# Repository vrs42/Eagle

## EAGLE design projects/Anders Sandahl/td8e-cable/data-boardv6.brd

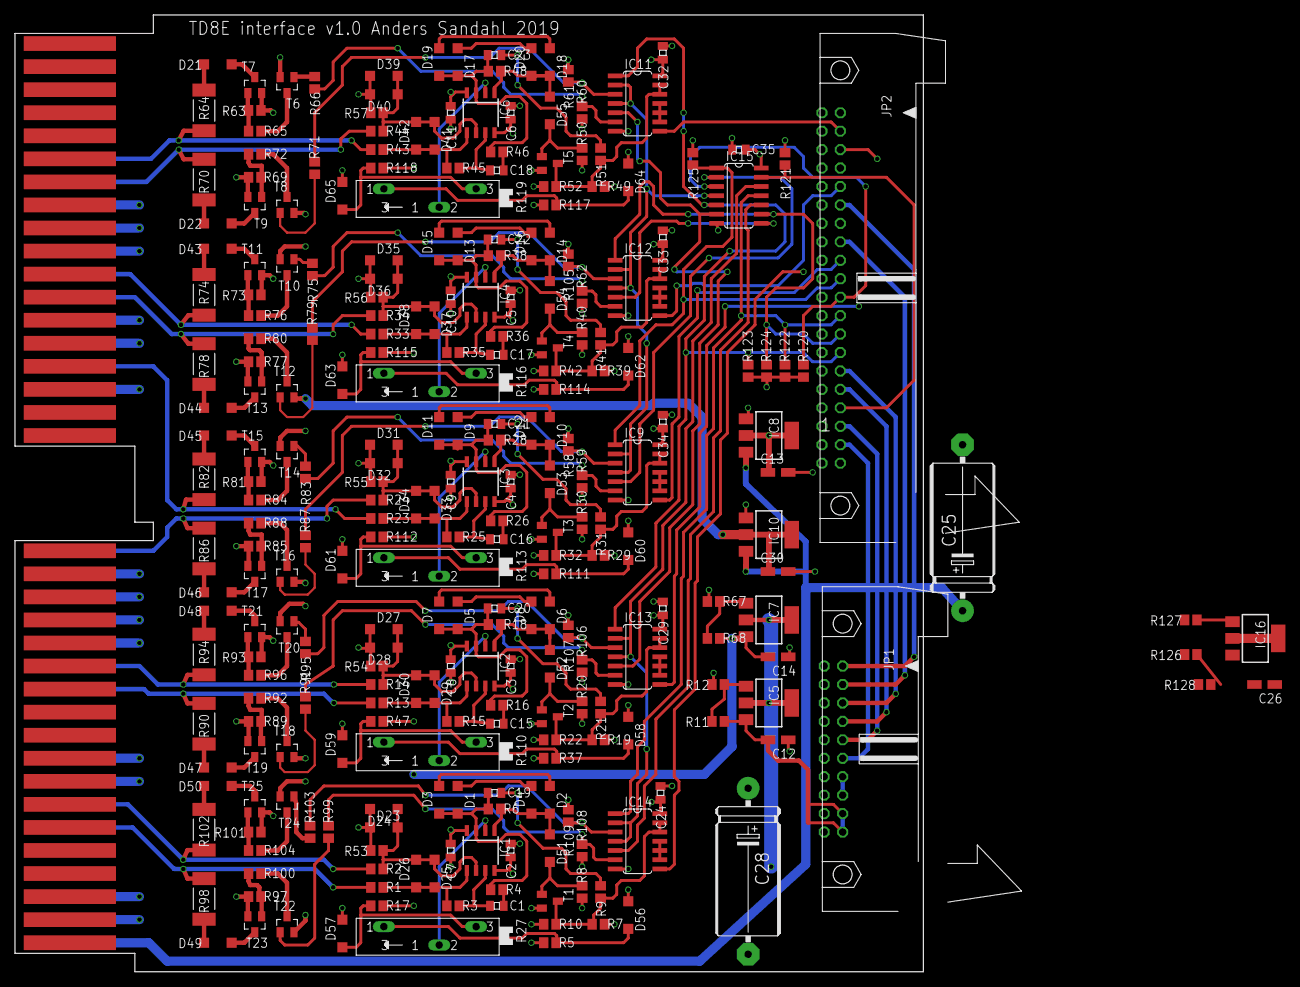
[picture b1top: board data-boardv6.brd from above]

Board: 4 copper layers, 125.1 x 131.8 mm, 270 parts (0 on the bottom side), 179 nets.

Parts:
C1, C15, C16, C17, C18: 10n; 0805
C2, C3, C4, C5, C6, C7, C8, C9, C10, C11, C24, C29, C32, C33, C34, C35: 100n; 0805
C12, C13, C14, C26, C30: 10u/10V; CT3216
C19, C20, C21, C22, C23: 10p; 0805
C25, C28: 330u; E22-9
D1, D2, D3, D4, D5, D6, D7, D8, D9, D10, D11, D12, D13, D14, D15, D16, D17, D18, D19, D20, D23, D24, D25, D26, D27, D28, D29, D30, D31, D32, D33, D34, D35, D36, D37, D38, D39, D40, D41, D42, D51, D52, D53, D54, D55, D56, D57, D58, D59, D60, D61, D62, D63, D64, D65: 1N4148; SOD123
D21, D22, D43, D44, D45, D46, D47, D48, D49, D50: MBR0540T1; SOD123
IC1, IC2, IC3, IC4, IC6: OPA2134D; SOIC8
IC5: LM337; SOT223@1
IC7: LM337; SOT223@2
IC8: LM1117-5; SOT223@3
IC9, IC11, IC12, IC13, IC14: 7400D; SO14
IC10: LM1117-3.3; SOT223@3
IC15: 7404D; SO14
IC16: LM337; SOT223
J1: FLIPCHIP_2; FLIPCHIP-21
JP1: 2Z10/90-FRAMED
JP2: 2X20/90-FRAMED
R1, R2, R13, R14, R23, R24, R33, R34, R43, R44: 220; R0805
R3, R15, R25, R35, R45, R53, R54, R55, R56, R57: 22k; R0805
R4, R8, R16, R20, R26, R30, R36, R40, R46, R50: 4k7; R0805
R5, R17, R37, R47, R111, R112, R114, R115, R117, R118: 2k2; R0805
R6, R9, R18, R21, R28, R31, R38, R41, R48, R51: 470k; R0805
R7, R19, R29, R39, R49: 3k; R0805
R10, R22, R32, R42, R52, R58, R59, R60, R61, R62, R105, R106, R107, R108, R109: 1k; R0805
R11, R68, R127: 240; R0805
R12: 330; R0805
R27, R110, R113, R116, R119: 10k; SP19L
R63, R69, R73, R77, R81, R85, R89, R93, R97, R101: 150; R0805
R64, R70, R74, R78, R82, R86, R90, R94, R98, R102: 75 2W; R2512
R65, R72, R76, R80, R84, R88, R92, R96, R100, R104: 680; R0805
R66, R71, R75, R79, R83, R87, R91, R95, R99, R103: 6k8; R0805
R67: 720; R0805
R120, R121, R122, R123, R124, R125: 470; R0805
R126: 2k05; R0805
R128: 1k8; R0805
T1, T2, T3, T4, T5: BC847; SOT23
T6, T8, T10, T12, T14, T16, T18, T20, T22, T24: BC857B; SOT23
T7, T9, T11, T13, T15, T17, T19, T21, T23, T25: IRLML0100TR; SOT23

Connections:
+3.3V: C30.+, IC10.2, IC10.4, T6.2, T8.2, T10.2, T12.2, T14.2, T16.2, T18.2, T20.2, T22.2, T24.2
+10V: C25.+, IC8.3, IC10.3, J1.AA2
-3V: C12.-, IC5.3, JP1.18, JP1.20, R11.1
-12V: C26.-, IC16.3, R63.1, R69.1, R73.1, R77.1, R81.1, R85.1, R89.1, R93.1, R97.1, R101.1, R127.2, R128.2, T7.2, T9.2, T11.2, T13.2, T15.2, T17.2, T19.2, T21.2, T23.2, T25.2
-15V: C28.-, IC5.2, IC5.4, IC7.2, IC7.4, IC16.2, IC16.4, J1.AB2
CON_ALL_HALT_L: JP1.10, JP2.36
D0(0): J1.BP2, R43.1, R64.2
D0(1): J1.BN2, R44.1, R70.2
D1(0): J1.BJ2, R33.1, R74.2
D1(1): J1.BH2, R34.1, R78.2
D2(0): J1.BD2, R23.1, R82.2
D2(1): J1.AV2, R24.1, R86.2
DATA1: IC11.12, IC11.13, R49.1, R51.2, R52.2, T5.3
DATA2: IC12.12, IC12.13, R39.1, R41.2, R42.2, T4.3
DATA3: IC9.12, IC9.13, R29.1, R31.2, R32.2, T3.3
F/R(0)_H: JP1.12, JP2.38
GND: C2.1, C3.1, C4.1, C5.1, C6.1, C7.2, C8.2, C9.2, C10.2, C11.2, C12.+, C13.-, C14.+, C24.1, C25.-, C26.+, C28.+, C29.1, C30.-, C32.1, C33.1, C34.1, C35.1, D23.C, D24.A, D27.C, D28.A, D31.C, D32.A, D35.C, D36.A, D39.C, D40.A, D56.C, D57.A, D58.C, D59.A, D60.C, D61.A, D62.C, D63.A, D64.C, D65.A, IC8.1, IC9.7, IC10.1, IC11.7, IC12.7, IC13.7, IC14.7, IC15.7, J1.AC2, J1.AJ2, J1.AK2, J1.AR2, J1.AS2, J1.AT2, J1.AU2, J1.BC2, J1.BE2, J1.BF2, J1.BK2, J1.BL2, J1.BM2, JP1.1, JP1.3, JP1.5, JP1.7, JP1.9, JP1.11, JP1.13, JP1.15, JP1.17, JP1.19, JP2.1, JP2.3, JP2.5, JP2.7, JP2.9, JP2.11, JP2.13, JP2.15, JP2.17, JP2.19, JP2.21, JP2.23, JP2.25, JP2.27, JP2.29, JP2.31, JP2.33, JP2.35, JP2.37, JP2.39, R7.2, R12.2, R19.2, R29.2, R39.2, R49.2, R53.2, R54.2, R55.2, R56.2, R57.2, R67.1, R126.1, R128.1, T1.2, T2.2, T3.2, T4.2, T5.2
MARK: IC13.12, IC13.13, R19.1, R21.2, R22.2, T2.3
MT(0): J1.AN2, R13.1, R90.2
MT(1): J1.AP2, R14.1, R94.2
unnamed: D25.A, D26.C, IC1.5, R1.2, R3.1
unnamed: R75.1, T10.1
unnamed: C1.1, IC1.7, R3.2
unnamed: D1.C, D4.A
unnamed: C19.1, D1.A, D3.C, IC1.3, R4.1, R6.1
unnamed: D43.A, R74.1
unnamed: D2.A, D4.C, D51.C, IC1.1, R6.2
unnamed: D51.A, R8.2, T1.1
unnamed: C19.2, R9.1
unnamed: C23.2, R51.1
unnamed: D2.C, D3.A
unnamed: C1.2, R4.2
unnamed: D43.C, T11.3
unnamed: R76.2, T10.3
unnamed: R73.2, R76.1, T11.1
unnamed: R79.1, T12.1
unnamed: D44.A, R78.1
unnamed: D44.C, T13.3
unnamed: R80.2, T12.3
unnamed: R77.2, R80.1, T13.1
unnamed: IC5.1, R11.2, R12.1
unnamed: IC9.6, R59.2, R83.2
unnamed: R83.1, T14.1
unnamed: C15.1, IC2.7, R15.2
unnamed: D5.C, D8.A
unnamed: C20.1, D5.A, D7.C, IC2.3, R16.1, R18.1
unnamed: D6.A, D8.C, D52.C, IC2.1, R18.2
unnamed: D45.A, R82.1
unnamed: D52.A, R20.2, T2.1
unnamed: IC1.2, R27.S
unnamed: C22.2, R41.1
unnamed: C15.2, R16.2
unnamed: D45.C, T15.3
unnamed: D6.C, D7.A
unnamed: R84.2, T14.3
unnamed: C16.1, IC3.7, R25.2
unnamed: D9.C, D12.A
unnamed: C21.1, D9.A, D11.C, IC3.3, R26.1, R28.1
unnamed: D10.A, D12.C, D53.C, IC3.1, R28.2
unnamed: R81.2, R84.1, T15.1
unnamed: D53.A, R30.2, T3.1
unnamed: D56.A, R5.2, R27.A
unnamed: C16.2, R26.2
unnamed: IC11.9, IC11.10, IC11.11
unnamed: IC9.9, IC9.10, IC9.11
unnamed: D10.C, D11.A
unnamed: R87.1, T16.1
unnamed: C17.1, IC4.7, R35.2
unnamed: D13.C, D16.A
unnamed: C22.1, D13.A, D15.C, IC4.3, R36.1, R38.1
unnamed: D14.A, D16.C, D54.C, IC4.1, R38.2
unnamed: D46.A, R86.1
unnamed: D54.A, R40.2, T4.1
unnamed: C21.2, R31.1
unnamed: C17.2, R36.2
unnamed: IC14.5, IC15.10
unnamed: IC11.6, R60.2, R66.2
unnamed: D14.C, D15.A
unnamed: D46.C, T17.3
unnamed: C18.1, IC6.7, R45.2
unnamed: D17.C, D20.A
unnamed: C23.1, D17.A, D19.C, IC6.3, R46.1, R48.1
unnamed: D18.A, D20.C, D55.C, IC6.1, R48.2
unnamed: R88.2, T16.3
unnamed: D55.A, R50.2, T5.1
unnamed: D57.C, R17.1, R27.E
unnamed: C18.2, R46.2
unnamed: IC12.6, R62.2, R75.2
unnamed: IC13.9, IC13.10, IC13.11
unnamed: D18.C, D19.A
unnamed: IC13.6, R91.2, R106.2
unnamed: IC12.9, IC12.10, IC12.11
unnamed: IC13.3, R95.2, R107.2
unnamed: IC14.6, R99.2, R108.2
unnamed: IC14.3, R103.2, R109.2
unnamed: C20.2, R21.1
unnamed: IC2.2, R110.S
unnamed: D58.A, R37.2, R110.A
unnamed: D59.C, R47.1, R110.E
unnamed: D60.A, R111.2, R113.A
unnamed: D61.C, R112.1, R113.E
unnamed: D62.A, R114.2, R116.A
unnamed: D63.C, R115.1, R116.E
unnamed: D64.A, R117.2, R119.A
unnamed: D65.C, R118.1, R119.E
unnamed: R65.2, T6.3
unnamed: R63.2, R65.1, T7.1
unnamed: IC7.1, R67.2, R68.1
unnamed: R71.1, T8.1
unnamed: IC4.2, R116.S
unnamed: R66.1, T6.1
unnamed: D22.A, R70.1
unnamed: R85.2, R88.1, T17.1
unnamed: D21.A, R64.1
unnamed: D21.C, T7.3
unnamed: R91.1, T18.1
unnamed: D47.A, R90.1
unnamed: IC3.2, R113.S
unnamed: D47.C, T19.3
unnamed: R92.2, T18.3
unnamed: R89.2, R92.1, T19.1
unnamed: R95.1, T20.1
unnamed: D48.A, R94.1
unnamed: D48.C, T21.3
unnamed: R96.2, T20.3
unnamed: R93.2, R96.1, T21.1
unnamed: IC6.2, R119.S
unnamed: IC14.9, IC14.10, IC14.11
unnamed: IC12.5, IC15.8
unnamed: IC9.5, IC15.2
unnamed: IC16.1, R126.2, R127.1
unnamed: D22.C, T9.3
unnamed: R72.2, T8.3
unnamed: R69.2, R72.1, T9.1
unnamed: D23.A, D24.C, D25.C, D26.A, IC1.6, R2.2, R53.1
unnamed: D29.A, D30.C, IC2.5, R13.2, R15.1
unnamed: D27.A, D28.C, D29.C, D30.A, IC2.6, R14.2, R54.1
unnamed: R99.1, T22.1
unnamed: D49.A, R98.1
unnamed: D33.A, D34.C, IC3.5, R23.2, R25.1
unnamed: D31.A, D32.C, D33.C, D34.A, IC3.6, R24.2, R55.1
unnamed: D49.C, T23.3
unnamed: R100.2, T22.3
unnamed: D37.A, D38.C, IC4.5, R33.2, R35.1
unnamed: D35.A, D36.C, D37.C, D38.A, IC4.6, R34.2, R56.1
unnamed: R97.2, R100.1, T23.1
unnamed: R103.1, T24.1
unnamed: D41.A, D42.C, IC6.5, R43.2, R45.1
unnamed: D39.A, D40.C, D41.C, D42.A, IC6.6, R44.2, R57.1
unnamed: D50.A, R102.1
unnamed: D50.C, T25.3
unnamed: R104.2, T24.3
unnamed: R101.2, R104.1, T25.1
RD0: IC11.8, JP2.4
RD1: IC12.8, JP2.10
RD2: IC9.8, JP2.18
RMT: IC13.8, JP2.6
RTT: IC14.8, JP2.8
S/G(0)_H: JP1.6, JP2.30
SEL_ECHO: JP1.2, JP2.12
T/M_ENAB_H: IC13.2, IC13.4, IC14.2, IC14.4, IC15.12
T/M_ENAB_L: IC15.13, JP2.34, R121.2
TIMING: IC14.12, IC14.13, R7.1, R9.2, R10.2, T1.3
TT(0): J1.AF2, R1.1, R98.2
TT(1): J1.AH2, R2.1, R102.2
UNIT(1)_H: JP1.8, JP2.32
V+: C2.2, C3.2, C4.2, C5.2, C6.2, C13.+, C24.2, C29.2, C32.2, C33.2, C34.2, C35.2, IC1.8, IC2.8, IC3.8, IC4.8, IC6.8, IC8.2, IC8.4, IC9.14, IC11.14, IC12.14, IC13.14, IC14.14, IC15.14, JP1.14, JP1.16, R5.1, R8.1, R10.1, R20.1, R22.1, R30.1, R32.1, R37.1, R40.1, R42.1, R50.1, R52.1, R58.1, R59.1, R60.1, R61.1, R62.1, R105.1, R106.1, R107.1, R108.1, R109.1, R111.1, R114.1, R117.1, R120.1, R121.1, R122.1, R123.1, R124.1, R125.1
V-: C7.1, C8.1, C9.1, C10.1, C11.1, C14.-, IC1.4, IC2.4, IC3.4, IC4.4, IC6.4, IC7.3, R17.2, R47.2, R68.2, R112.2, R115.2, R118.2
WD0(0): IC11.5, IC13.5, IC15.6
WD0(1): IC11.1, IC13.1, IC15.5, JP2.28, R123.2
WD1(1): IC12.1, IC15.9, JP2.26, R124.2
WD2(1): IC9.1, IC15.1, JP2.20, R125.2
WD_ENAB: IC9.2, IC9.4, IC11.2, IC11.4, IC12.2, IC12.4, IC15.4
WD_ENAB_TD8E: IC15.3, JP2.22, R120.2
WRT_ECHO: JP1.4, JP2.16
WTT(1): IC14.1, IC15.11, JP2.24, R122.2
W_DATA1_P: IC11.3, R61.2, R71.2
W_DATA2_P: IC12.3, R79.2, R105.2
W_DATA3_P: IC9.3, R58.2, R87.2

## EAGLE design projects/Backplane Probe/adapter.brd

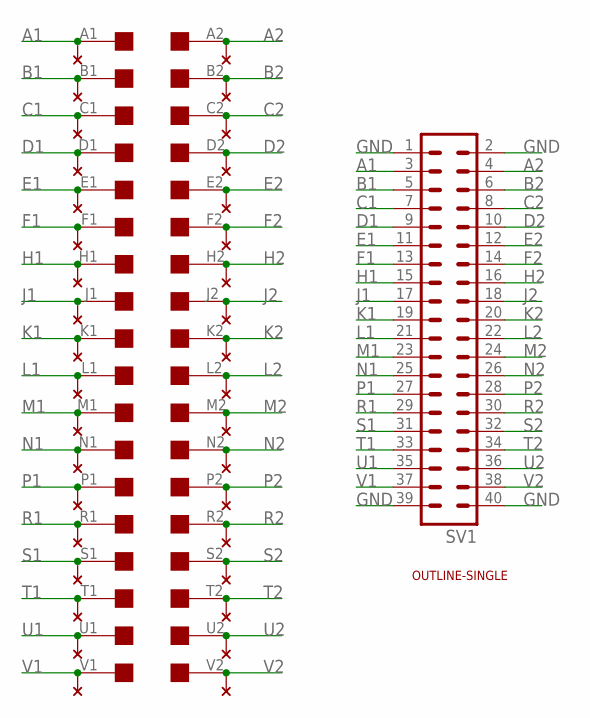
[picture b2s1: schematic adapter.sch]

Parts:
EDGE1: EDGE-2CONNECTOR; EDGE-CON2
SV1: MA20-2
U$2: OUTLINE-SINGLE; SINGLE
U$3: THRU-HOLE2; THRU-HOLEB

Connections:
A1: EDGE1.A1, SV1.3, U$3.A1
A2: EDGE1.A2, SV1.4, U$3.A2
B1: EDGE1.B1, SV1.5, U$3.B1
B2: EDGE1.B2, SV1.6, U$3.B2
C1: EDGE1.C1, SV1.7, U$3.C1
C2: EDGE1.C2, SV1.8, U$3.C2
D1: EDGE1.D1, SV1.9, U$3.D1
D2: EDGE1.D2, SV1.10, U$3.D2
E1: EDGE1.E1, SV1.11, U$3.E1
E2: EDGE1.E2, SV1.12, U$3.E2
F1: EDGE1.F1, SV1.13, U$3.F1
F2: EDGE1.F2, SV1.14, U$3.F2
GND: SV1.1, SV1.2, SV1.39, SV1.40
H1: EDGE1.H1, SV1.15, U$3.H1
H2: EDGE1.H2, SV1.16, U$3.H2
J1: EDGE1.J1, SV1.17, U$3.J1
J2: EDGE1.J2, SV1.18, U$3.J2
K1: EDGE1.K1, SV1.19, U$3.K1
K2: EDGE1.K2, SV1.20, U$3.K2
L1: EDGE1.L1, SV1.21, U$3.L1
L2: EDGE1.L2, SV1.22, U$3.L2
M1: EDGE1.M1, SV1.23, U$3.M1
M2: EDGE1.M2, SV1.24, U$3.M2
N1: EDGE1.N1, SV1.25, U$3.N1
N2: EDGE1.N2, SV1.26, U$3.N2
P1: EDGE1.P1, SV1.27, U$3.P1
P2: EDGE1.P2, SV1.28, U$3.P2
R1: EDGE1.R1, SV1.29, U$3.R1
R2: EDGE1.R2, SV1.30, U$3.R2
S1: EDGE1.S1, SV1.31, U$3.S1
S2: EDGE1.S2, SV1.32, U$3.S2
T1: EDGE1.T1, SV1.33, U$3.T1
T2: EDGE1.T2, SV1.34, U$3.T2
U1: EDGE1.U1, SV1.35, U$3.U1
U2: EDGE1.U2, SV1.36, U$3.U2
V1: EDGE1.V1, SV1.37, U$3.V1
V2: EDGE1.V2, SV1.38, U$3.V2

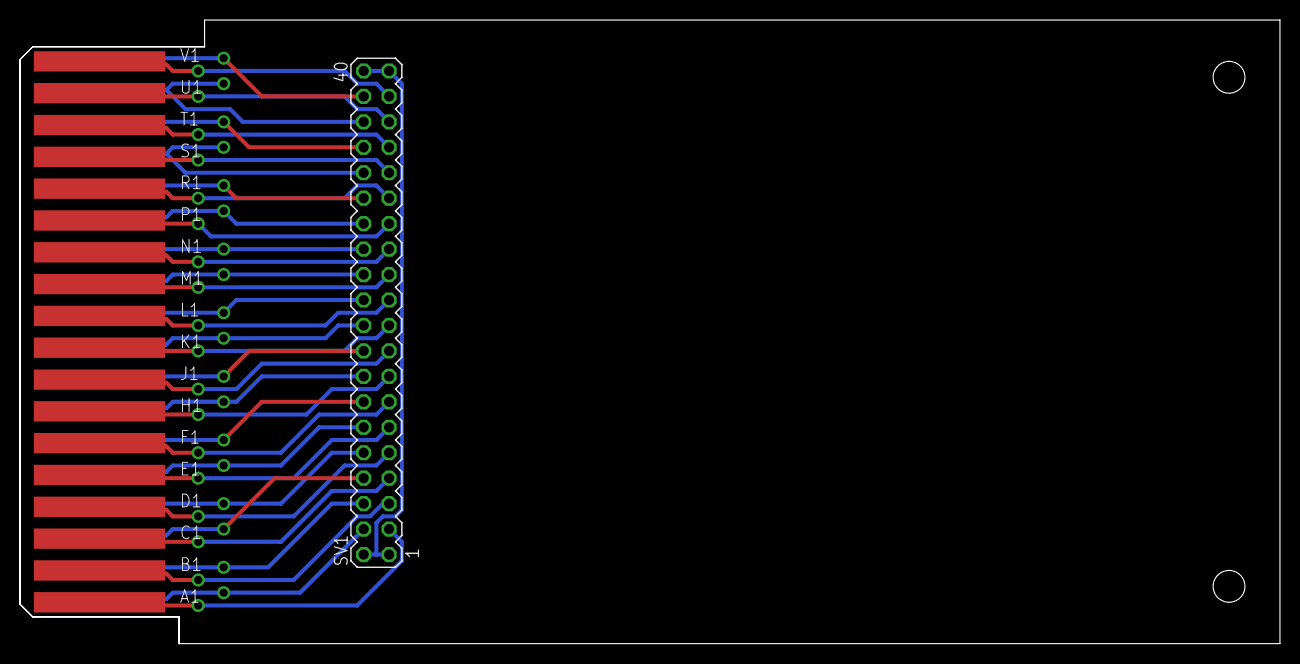
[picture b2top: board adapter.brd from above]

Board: 2 copper layers, 125.7 x 62.2 mm, 4 parts (0 on the bottom side), 37 nets.

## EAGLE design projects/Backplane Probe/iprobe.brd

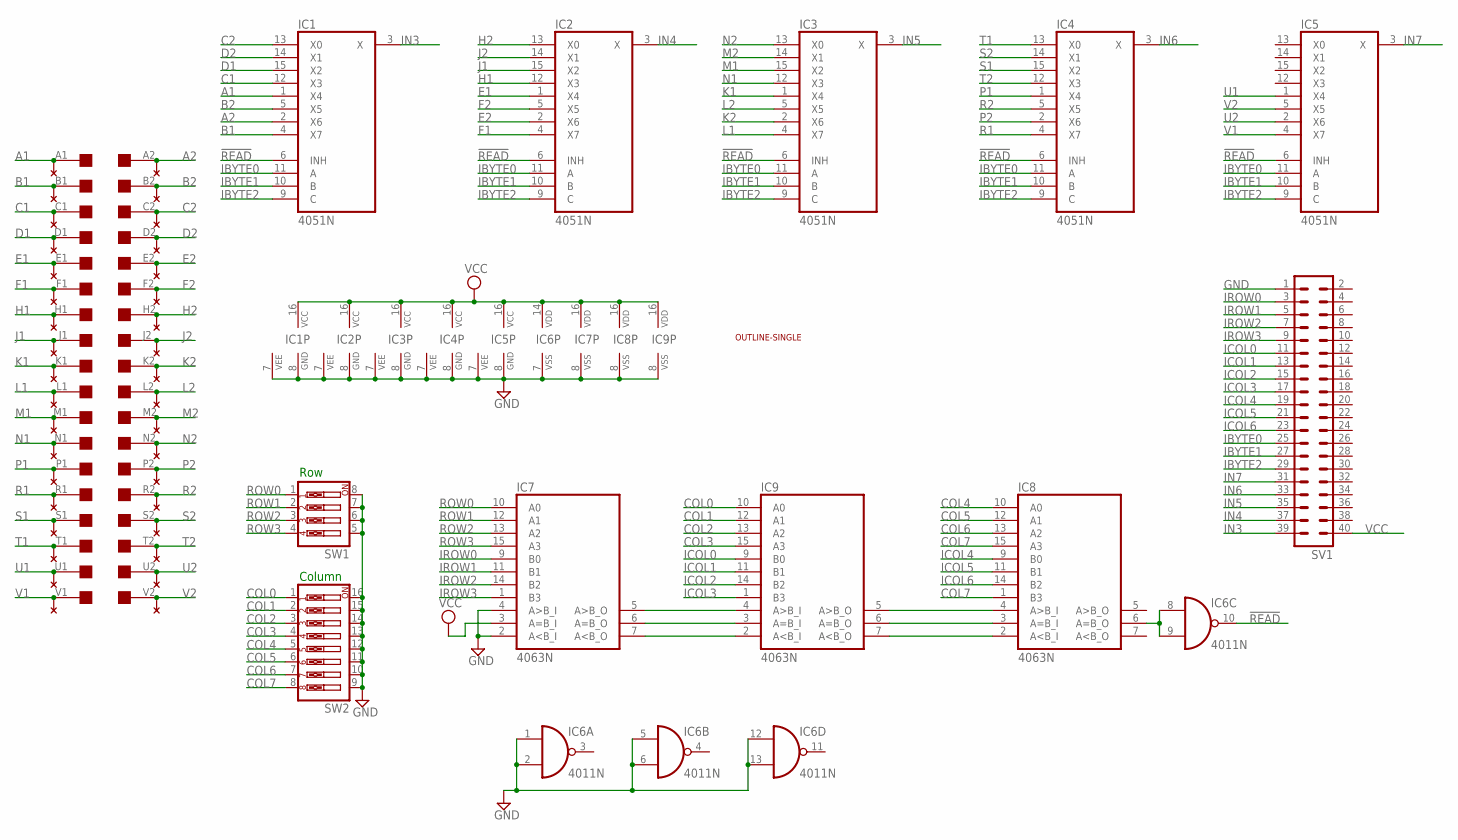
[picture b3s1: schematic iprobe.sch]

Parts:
EDGE1: EDGE-2CONNECTOR; EDGE-CON2
IC1, IC2, IC3, IC4, IC5: 4051N; DIL16
IC6: 4011N; DIL14
IC7, IC8, IC9: 4063N; DIL16
SV1: MA20-2
SW1: SW_DIP-4; EDG-04
SW2: SW_DIP-8; EDG-08
U$2: THRU-HOLE2; THRU-HOLEB
U$3: OUTLINE-SINGLE; SINGLE

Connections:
!READ: IC1.6 (INH), IC2.6 (INH), IC3.6 (INH), IC4.6 (INH), IC5.6 (INH), IC6.10 (O)
A1: EDGE1.A1, IC1.1 (X4), U$2.A1
A2: EDGE1.A2, IC1.2 (X6), U$2.A2
B1: EDGE1.B1, IC1.4 (X7), U$2.B1
B2: EDGE1.B2, IC1.5 (X5), U$2.B2
C1: EDGE1.C1, IC1.12 (X3), U$2.C1
C2: EDGE1.C2, IC1.13 (X0), U$2.C2
COL0: IC9.10 (A0), SW2.1
COL1: IC9.12 (A1), SW2.2
COL2: IC9.13 (A2), SW2.3
COL3: IC9.15 (A3), SW2.4
COL4: IC8.10 (A0), SW2.5
COL5: IC8.12 (A1), SW2.6
COL6: IC8.13 (A2), SW2.7
COL7: IC8.1 (B3), IC8.15 (A3), SW2.8
D1: EDGE1.D1, IC1.15 (X2), U$2.D1
D2: EDGE1.D2, IC1.14 (X1), U$2.D2
E1: EDGE1.E1, IC2.1 (X4), U$2.E1
E2: EDGE1.E2, IC2.2 (X6), U$2.E2
F1: EDGE1.F1, IC2.4 (X7), U$2.F1
F2: EDGE1.F2, IC2.5 (X5), U$2.F2
GND: IC1.7 (VEE), IC1.8 (GND), IC2.7 (VEE), IC2.8 (GND), IC3.7 (VEE), IC3.8 (GND), IC4.7 (VEE), IC4.8 (GND), IC5.7 (VEE), IC5.8 (GND), IC6.1 (I0), IC6.2 (I1), IC6.5 (I0), IC6.6 (I1), IC6.7 (VSS), IC6.12 (I0), IC6.13 (I1), IC7.2 (A<B_I), IC7.4 (A>B_I), IC7.8 (VSS), IC8.8 (VSS), IC9.8 (VSS), SV1.1, SW1.5, SW1.6, SW1.7, SW1.8, SW2.9, SW2.10, SW2.11, SW2.12, SW2.13, SW2.14, SW2.15, SW2.16
H1: EDGE1.H1, IC2.12 (X3), U$2.H1
H2: EDGE1.H2, IC2.13 (X0), U$2.H2
IBYTE0: IC1.11 (A), IC2.11 (A), IC3.11 (A), IC4.11 (A), IC5.11 (A), SV1.25
IBYTE1: IC1.10 (B), IC2.10 (B), IC3.10 (B), IC4.10 (B), IC5.10 (B), SV1.27
IBYTE2: IC1.9 (C), IC2.9 (C), IC3.9 (C), IC4.9 (C), IC5.9 (C), SV1.29
ICOL0: IC9.9 (B0), SV1.11
ICOL1: IC9.11 (B1), SV1.13
ICOL2: IC9.14 (B2), SV1.15
ICOL3: IC9.1 (B3), SV1.17
ICOL4: IC8.9 (B0), SV1.19
ICOL5: IC8.11 (B1), SV1.21
ICOL6: IC8.14 (B2), SV1.23
IN3: IC1.3 (X), SV1.39
IN4: IC2.3 (X), SV1.37
IN5: IC3.3 (X), SV1.35
IN6: IC4.3 (X), SV1.33
IN7: IC5.3 (X), SV1.31
IROW0: IC7.9 (B0), SV1.3
IROW1: IC7.11 (B1), SV1.5
IROW2: IC7.14 (B2), SV1.7
IROW3: IC7.1 (B3), SV1.9
J1: EDGE1.J1, IC2.15 (X2), U$2.J1
J2: EDGE1.J2, IC2.14 (X1), U$2.J2
K1: EDGE1.K1, IC3.1 (X4), U$2.K1
K2: EDGE1.K2, IC3.2 (X6), U$2.K2
L1: EDGE1.L1, IC3.4 (X7), U$2.L1
L2: EDGE1.L2, IC3.5 (X5), U$2.L2
M1: EDGE1.M1, IC3.15 (X2), U$2.M1
M2: EDGE1.M2, IC3.14 (X1), U$2.M2
N1: EDGE1.N1, IC3.12 (X3), U$2.N1
N2: EDGE1.N2, IC3.13 (X0), U$2.N2
unnamed: IC7.5 (A>B_O), IC9.4 (A>B_I)
unnamed: IC7.6 (A=B_O), IC9.3 (A=B_I)
unnamed: IC7.7 (A<B_O), IC9.2 (A<B_I)
unnamed: IC6.8 (I0), IC6.9 (I1), IC8.6 (A=B_O)
unnamed: IC8.4 (A>B_I), IC9.5 (A>B_O)
unnamed: IC8.3 (A=B_I), IC9.6 (A=B_O)
unnamed: IC8.2 (A<B_I), IC9.7 (A<B_O)
P1: EDGE1.P1, IC4.1 (X4), U$2.P1
P2: EDGE1.P2, IC4.2 (X6), U$2.P2
R1: EDGE1.R1, IC4.4 (X7), U$2.R1
R2: EDGE1.R2, IC4.5 (X5), U$2.R2
ROW0: IC7.10 (A0), SW1.1
ROW1: IC7.12 (A1), SW1.2
ROW2: IC7.13 (A2), SW1.3
ROW3: IC7.15 (A3), SW1.4
S1: EDGE1.S1, IC4.15 (X2), U$2.S1
S2: EDGE1.S2, IC4.14 (X1), U$2.S2
T1: EDGE1.T1, IC4.13 (X0), U$2.T1
T2: EDGE1.T2, IC4.12 (X3), U$2.T2
U1: EDGE1.U1, IC5.1 (X4), U$2.U1
U2: EDGE1.U2, IC5.2 (X6), U$2.U2
V1: EDGE1.V1, IC5.4 (X7), U$2.V1
V2: EDGE1.V2, IC5.5 (X5), U$2.V2
VCC: IC1.16 (VCC), IC2.16 (VCC), IC3.16 (VCC), IC4.16 (VCC), IC5.16 (VCC), IC6.14 (VDD), IC7.3 (A=B_I), IC7.16 (VDD), IC8.16 (VDD), IC9.16 (VDD), SV1.40

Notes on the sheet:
Row
Column

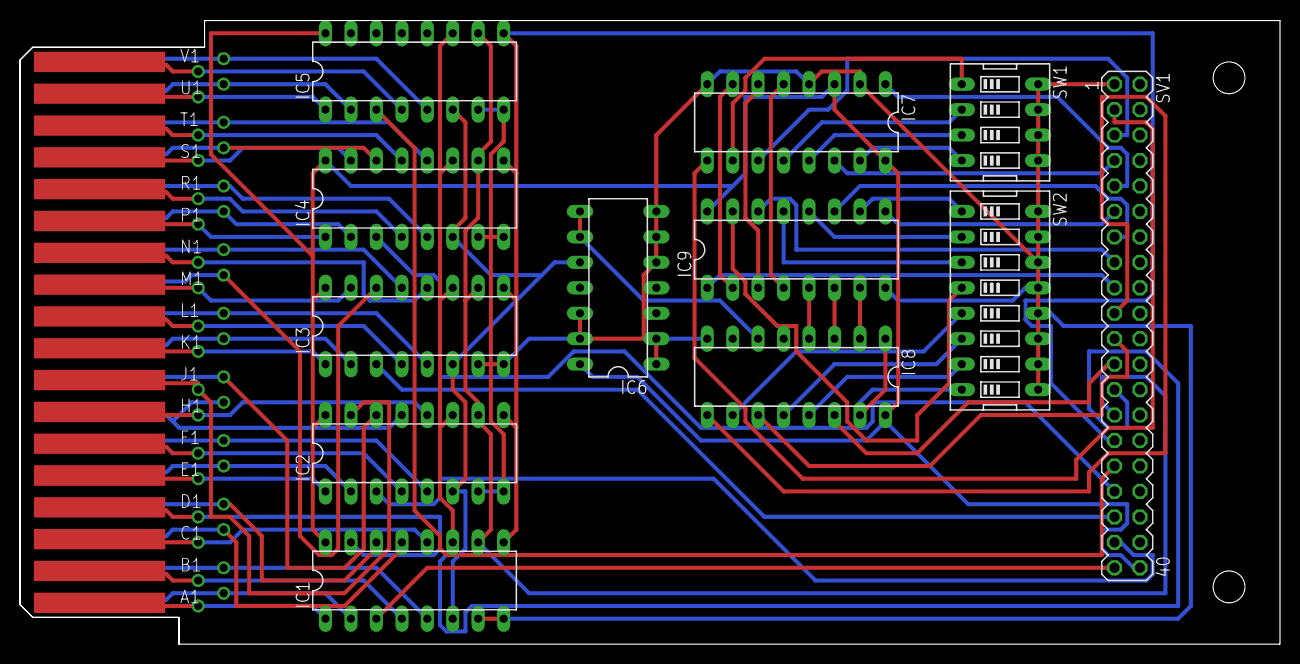
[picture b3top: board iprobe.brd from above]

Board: 2 copper layers, 125.7 x 62.2 mm, 15 parts (0 on the bottom side), 77 nets.

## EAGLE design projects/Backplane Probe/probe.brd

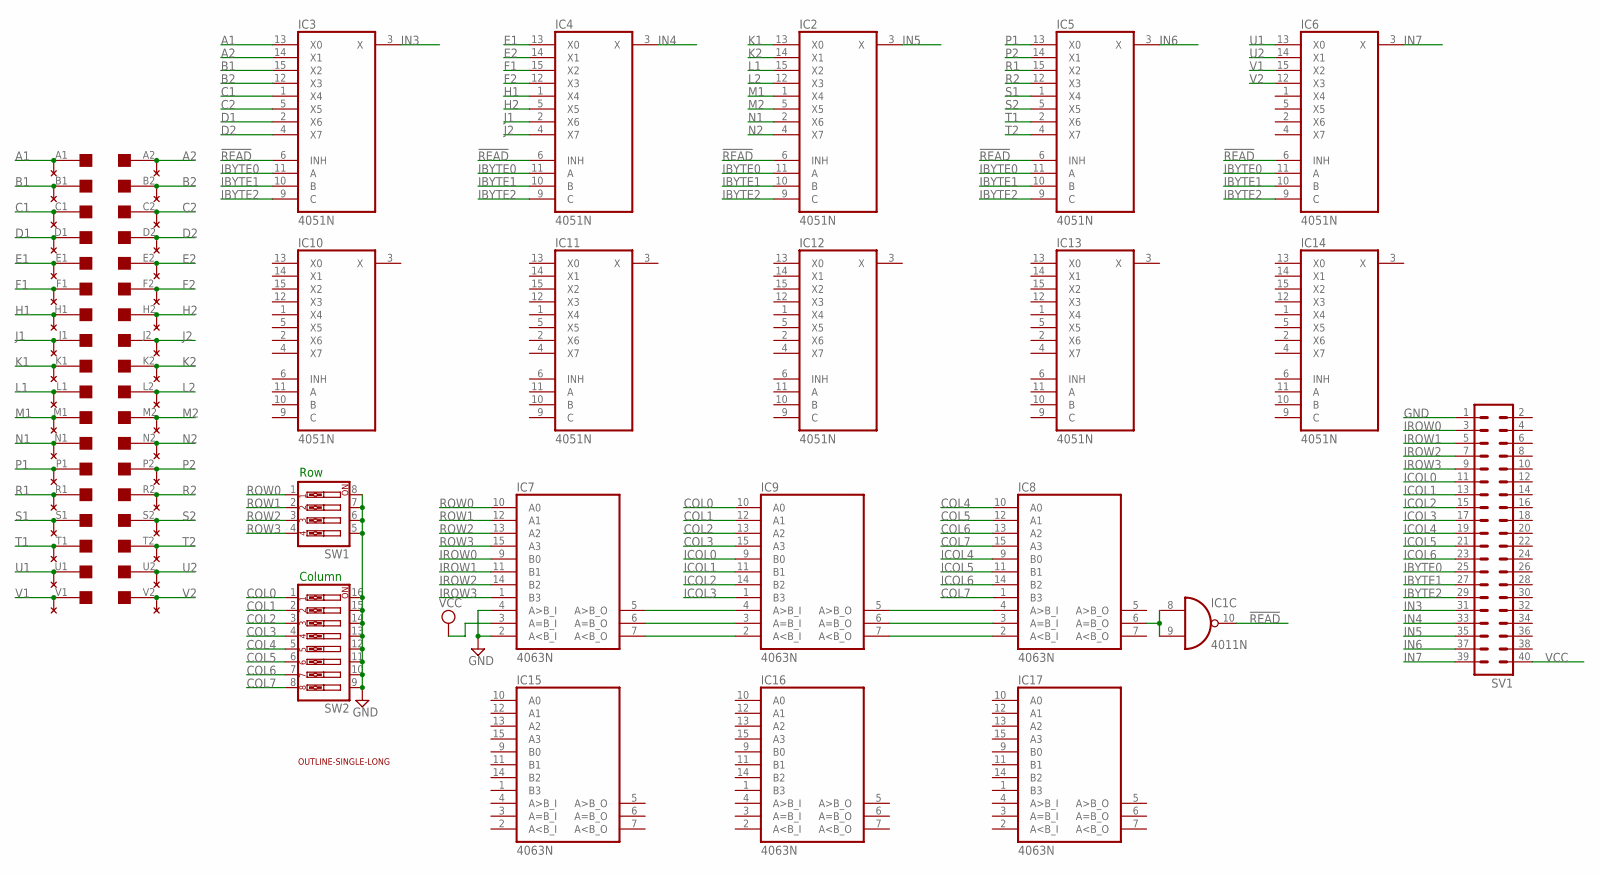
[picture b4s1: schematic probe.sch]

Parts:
EDGE1: EDGE-2CONNECTOR; EDGE-CON2
IC1: 4011N; DIL14
IC2, IC3, IC4, IC5, IC6, IC10, IC11, IC12, IC13, IC14: 4051N; DIL16
IC7, IC8, IC9, IC15, IC16, IC17: 4063N; DIL16
SV1: MA20-2
SW1: SW_DIP-4; EDG-04
SW2: SW_DIP-8; EDG-08
U$1: OUTLINE-SINGLE-LONG; SINGLE-LONG
U$3: THRU-HOLE2; THRU-HOLEB

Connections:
!READ: IC1.10 (O), IC2.6 (INH), IC3.6 (INH), IC4.6 (INH), IC5.6 (INH), IC6.6 (INH)
A1: EDGE1.A1, IC3.13 (X0), U$3.A1
A2: EDGE1.A2, IC3.14 (X1), U$3.A2
B1: EDGE1.B1, IC3.15 (X2), U$3.B1
B2: EDGE1.B2, IC3.12 (X3), U$3.B2
C1: EDGE1.C1, IC3.1 (X4), U$3.C1
C2: EDGE1.C2, IC3.5 (X5), U$3.C2
COL0: IC9.10 (A0), SW2.1
COL1: IC9.12 (A1), SW2.2
COL2: IC9.13 (A2), SW2.3
COL3: IC9.15 (A3), SW2.4
COL4: IC8.10 (A0), SW2.5
COL5: IC8.12 (A1), SW2.6
COL6: IC8.13 (A2), SW2.7
COL7: IC8.1 (B3), IC8.15 (A3), SW2.8
D1: EDGE1.D1, IC3.2 (X6), U$3.D1
D2: EDGE1.D2, IC3.4 (X7), U$3.D2
E1: EDGE1.E1, IC4.13 (X0), U$3.E1
E2: EDGE1.E2, IC4.14 (X1), U$3.E2
F1: EDGE1.F1, IC4.15 (X2), U$3.F1
F2: EDGE1.F2, IC4.12 (X3), U$3.F2
GND: IC2.8 (GND), IC3.8 (GND), IC4.8 (GND), IC5.8 (GND), IC6.8 (GND), IC7.2 (A<B_I), IC7.4 (A>B_I), IC10.8 (GND), IC11.8 (GND), IC12.8 (GND), IC13.8 (GND), IC14.8 (GND), SV1.1, SW1.5, SW1.6, SW1.7, SW1.8, SW2.9, SW2.10, SW2.11, SW2.12, SW2.13, SW2.14, SW2.15, SW2.16
H1: EDGE1.H1, IC4.1 (X4), U$3.H1
H2: EDGE1.H2, IC4.5 (X5), U$3.H2
IBYTE0: IC2.11 (A), IC3.11 (A), IC4.11 (A), IC5.11 (A), IC6.11 (A), SV1.25
IBYTE1: IC2.10 (B), IC3.10 (B), IC4.10 (B), IC5.10 (B), IC6.10 (B), SV1.27
IBYTE2: IC2.9 (C), IC3.9 (C), IC4.9 (C), IC5.9 (C), IC6.9 (C), SV1.29
ICOL0: IC9.9 (B0), SV1.11
ICOL1: IC9.11 (B1), SV1.13
ICOL2: IC9.14 (B2), SV1.15
ICOL3: IC9.1 (B3), SV1.17
ICOL4: IC8.9 (B0), SV1.19
ICOL5: IC8.11 (B1), SV1.21
ICOL6: IC8.14 (B2), SV1.23
IN3: IC3.3 (X), SV1.31
IN4: IC4.3 (X), SV1.33
IN5: IC2.3 (X), SV1.35
IN6: IC5.3 (X), SV1.37
IN7: IC6.3 (X), SV1.39
IROW0: IC7.9 (B0), SV1.3
IROW1: IC7.11 (B1), SV1.5
IROW2: IC7.14 (B2), SV1.7
IROW3: IC7.1 (B3), SV1.9
J1: EDGE1.J1, IC4.2 (X6), U$3.J1
J2: EDGE1.J2, IC4.4 (X7), U$3.J2
K1: EDGE1.K1, IC2.13 (X0), U$3.K1
K2: EDGE1.K2, IC2.14 (X1), U$3.K2
L1: EDGE1.L1, IC2.15 (X2), U$3.L1
L2: EDGE1.L2, IC2.12 (X3), U$3.L2
M1: EDGE1.M1, IC2.1 (X4), U$3.M1
M2: EDGE1.M2, IC2.5 (X5), U$3.M2
N1: EDGE1.N1, IC2.2 (X6), U$3.N1
N2: EDGE1.N2, IC2.4 (X7), U$3.N2
unnamed: IC7.5 (A>B_O), IC9.4 (A>B_I)
unnamed: IC7.6 (A=B_O), IC9.3 (A=B_I)
unnamed: IC7.7 (A<B_O), IC9.2 (A<B_I)
unnamed: IC1.8 (I0), IC1.9 (I1), IC8.6 (A=B_O)
unnamed: IC8.4 (A>B_I), IC9.5 (A>B_O)
unnamed: IC8.3 (A=B_I), IC9.6 (A=B_O)
unnamed: IC8.2 (A<B_I), IC9.7 (A<B_O)
P1: EDGE1.P1, IC5.13 (X0), U$3.P1
P2: EDGE1.P2, IC5.14 (X1), U$3.P2
R1: EDGE1.R1, IC5.15 (X2), U$3.R1
R2: EDGE1.R2, IC5.12 (X3), U$3.R2
ROW0: IC7.10 (A0), SW1.1
ROW1: IC7.12 (A1), SW1.2
ROW2: IC7.13 (A2), SW1.3
ROW3: IC7.15 (A3), SW1.4
S1: EDGE1.S1, IC5.1 (X4), U$3.S1
S2: EDGE1.S2, IC5.5 (X5), U$3.S2
T1: EDGE1.T1, IC5.2 (X6), U$3.T1
T2: EDGE1.T2, IC5.4 (X7), U$3.T2
U1: EDGE1.U1, IC6.13 (X0), U$3.U1
U2: EDGE1.U2, IC6.14 (X1), U$3.U2
V1: EDGE1.V1, IC6.15 (X2), U$3.V1
V2: EDGE1.V2, IC6.12 (X3), U$3.V2
VCC: IC2.16 (VCC), IC3.16 (VCC), IC4.16 (VCC), IC5.16 (VCC), IC6.16 (VCC), IC7.3 (A=B_I), IC10.16 (VCC), IC11.16 (VCC), IC12.16 (VCC), IC13.16 (VCC), IC14.16 (VCC), SV1.40
VDD: IC1.14 (VDD), IC7.16 (VDD), IC8.16 (VDD), IC9.16 (VDD), IC15.16 (VDD), IC16.16 (VDD), IC17.16 (VDD)
VEE: IC2.7 (VEE), IC3.7 (VEE), IC4.7 (VEE), IC5.7 (VEE), IC6.7 (VEE), IC10.7 (VEE), IC11.7 (VEE), IC12.7 (VEE), IC13.7 (VEE), IC14.7 (VEE)
VSS: IC1.7 (VSS), IC7.8 (VSS), IC8.8 (VSS), IC9.8 (VSS), IC15.8 (VSS), IC16.8 (VSS), IC17.8 (VSS)

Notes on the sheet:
Row
Column

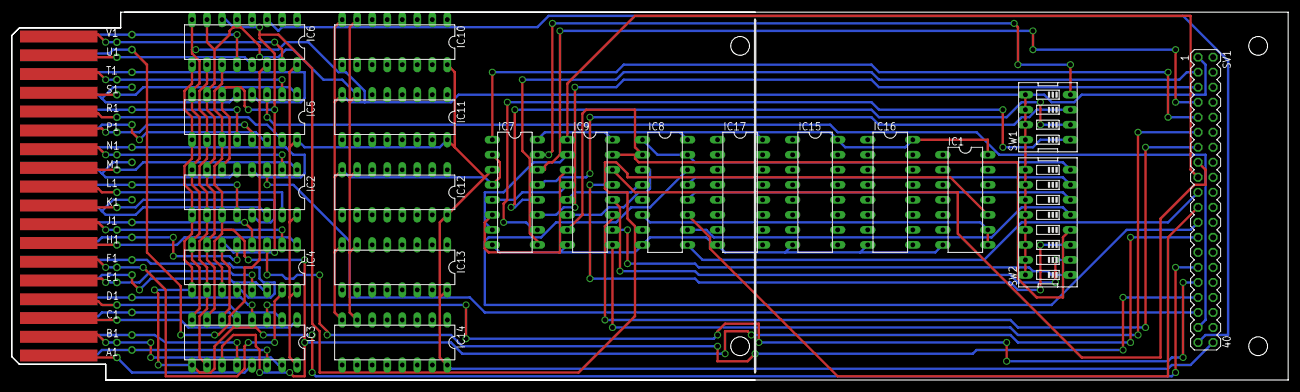
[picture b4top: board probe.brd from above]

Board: 2 copper layers, 215.9 x 62.2 mm, 23 parts (0 on the bottom side), 80 nets.

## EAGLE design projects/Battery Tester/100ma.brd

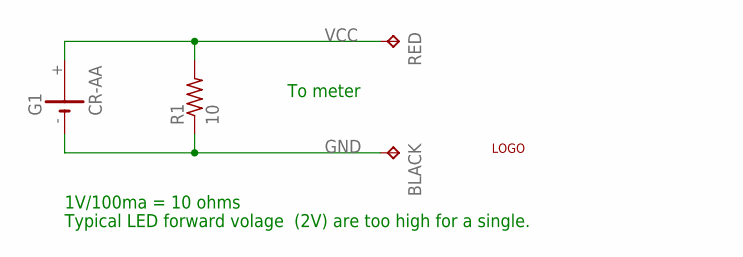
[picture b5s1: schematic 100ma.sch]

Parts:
BLACK: TPB2,54; B2,54
G1: CR-AA; CRAA
LOGO: LOGO
R1: 10; 0207/10
RED: TPB2,54; B2,54

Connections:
GND: BLACK.TP, G1.-, R1.1
VCC: G1.+, R1.2, RED.TP

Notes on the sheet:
1V/100ma = 10 ohms
To meter
Typical LED forward volage (2V) are too high for a single.

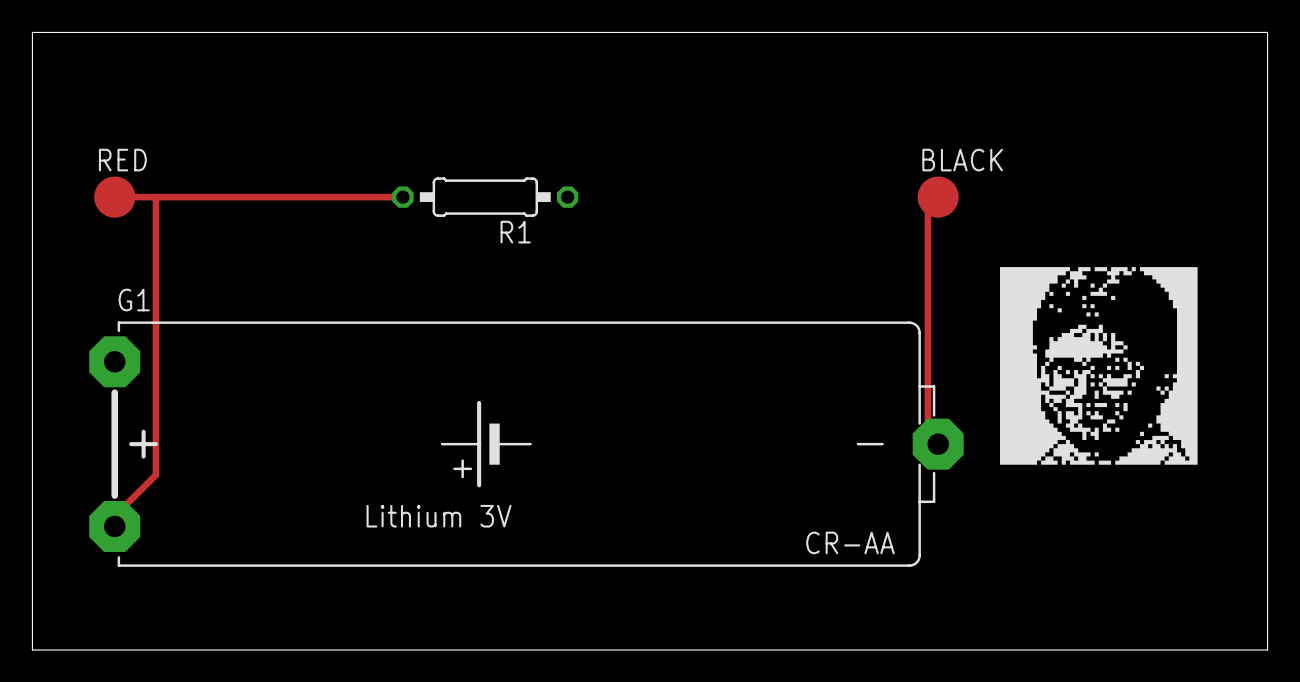
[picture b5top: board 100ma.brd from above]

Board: 2 copper layers, 76.2 x 38.1 mm, 5 parts (0 on the bottom side), 2 nets.

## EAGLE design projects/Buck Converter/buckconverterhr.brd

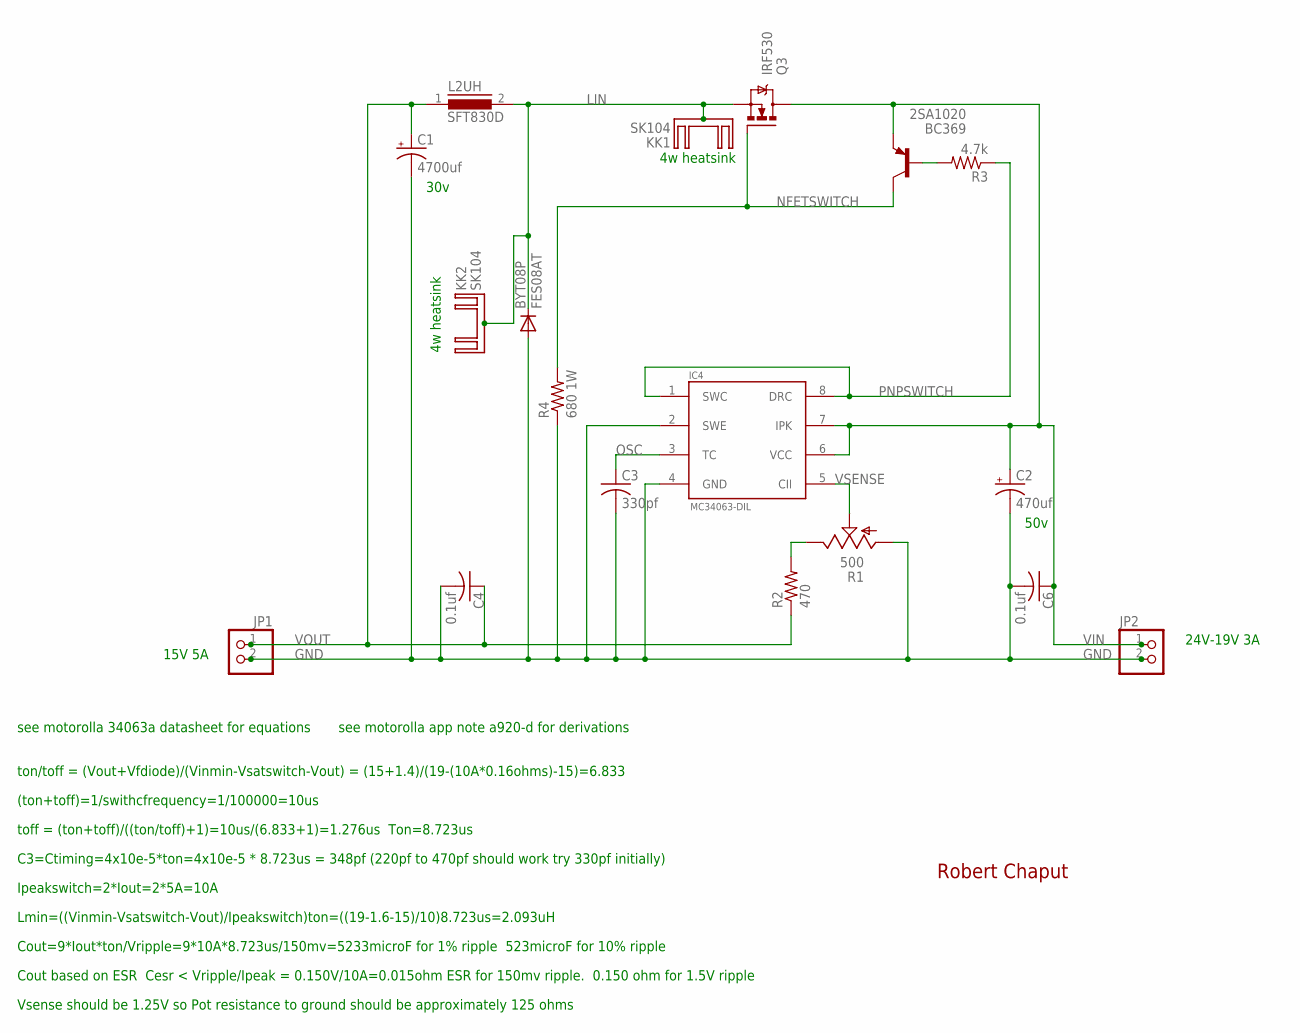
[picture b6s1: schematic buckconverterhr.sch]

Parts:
2SA1020: BC369; TO92-BCE
BYT08P: FES08AT; DO220S
C1: 4700uf; EB30D
C2: 470uf; E5-8,5
C3: 330pf; C050-030X075
C4, C6: 0.1uf; C050-030X075
IC4: MC34063-DIL; DIL08
JP1, JP2: PINHD-1X2; 1X02
KK1, KK2: SK104
L2UH: SFT830D
Q3: IRF530; TO220BV
R1: 500; PT-SPIN
R2: 470; 0309V
R3: 4.7k; 0309V
R4: 680 1W; P0613V

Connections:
GND: BYT08P.A, C1.-, C2.-, C3.2, C4.2, C6.2, IC4.2 (SWE), IC4.4 (GND), JP1.2, JP2.2, R1.A, R4.1
LIN: BYT08P.C, L2UH.2, Q3.S
unnamed: R1.E, R2.2
unnamed: 2SA1020.B, R3.2
NFETSWITCH: 2SA1020.C, Q3.G, R4.2
OSC: C3.1, IC4.3 (TC)
PNPSWITCH: IC4.1 (SWC), IC4.8 (DRC), R3.1
VIN: 2SA1020.E, C2.+, C6.1, IC4.6 (VCC), IC4.7 (IPK), JP2.1, Q3.D
VOUT: C1.+, C4.1, JP1.1, L2UH.1, R2.1
VSENSE: IC4.5 (CII), R1.S

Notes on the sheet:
4w heatsink
24V-19V 3A
15V 5A
ton/toff = (Vout+Vfdiode)/(Vinmin-Vsatswitch-Vout) = (15+1.4)/(19-(10A*0.16ohms)-15)=6.833
(ton+toff)=1/swithcfrequency=1/100000=10us
toff = (ton+toff)/((ton/toff)+1)=10us/(6.833+1)=1.276us Ton=8.723us
C3=Ctiming=4x10e-5*ton=4x10e-5 * 8.723us = 348pf (220pf to 470pf should work try 330pf initially)
Ipeakswitch=2*Iout=2*5A=10A
Lmin=((Vinmin-Vsatswitch-Vout)/Ipeakswitch)ton=((19-1.6-15)/10)8.723us=2.093uH
see motorolla 34063a datasheet for equations
see motorolla app note a920-d for derivations
Cout=9*Iout*ton/Vripple=9*10A*8.723us/150mv=5233microF for 1% ripple 523microF for 10% ripple
Cout based on ESR Cesr < Vripple/Ipeak = 0.150V/10A=0.015ohm ESR for 150mv ripple. 0.150 ohm for 1.5V ripple
Vsense should be 1.25V so Pot resistance to ground should be approximately 125 ohms
50v
30v
Robert Chaput

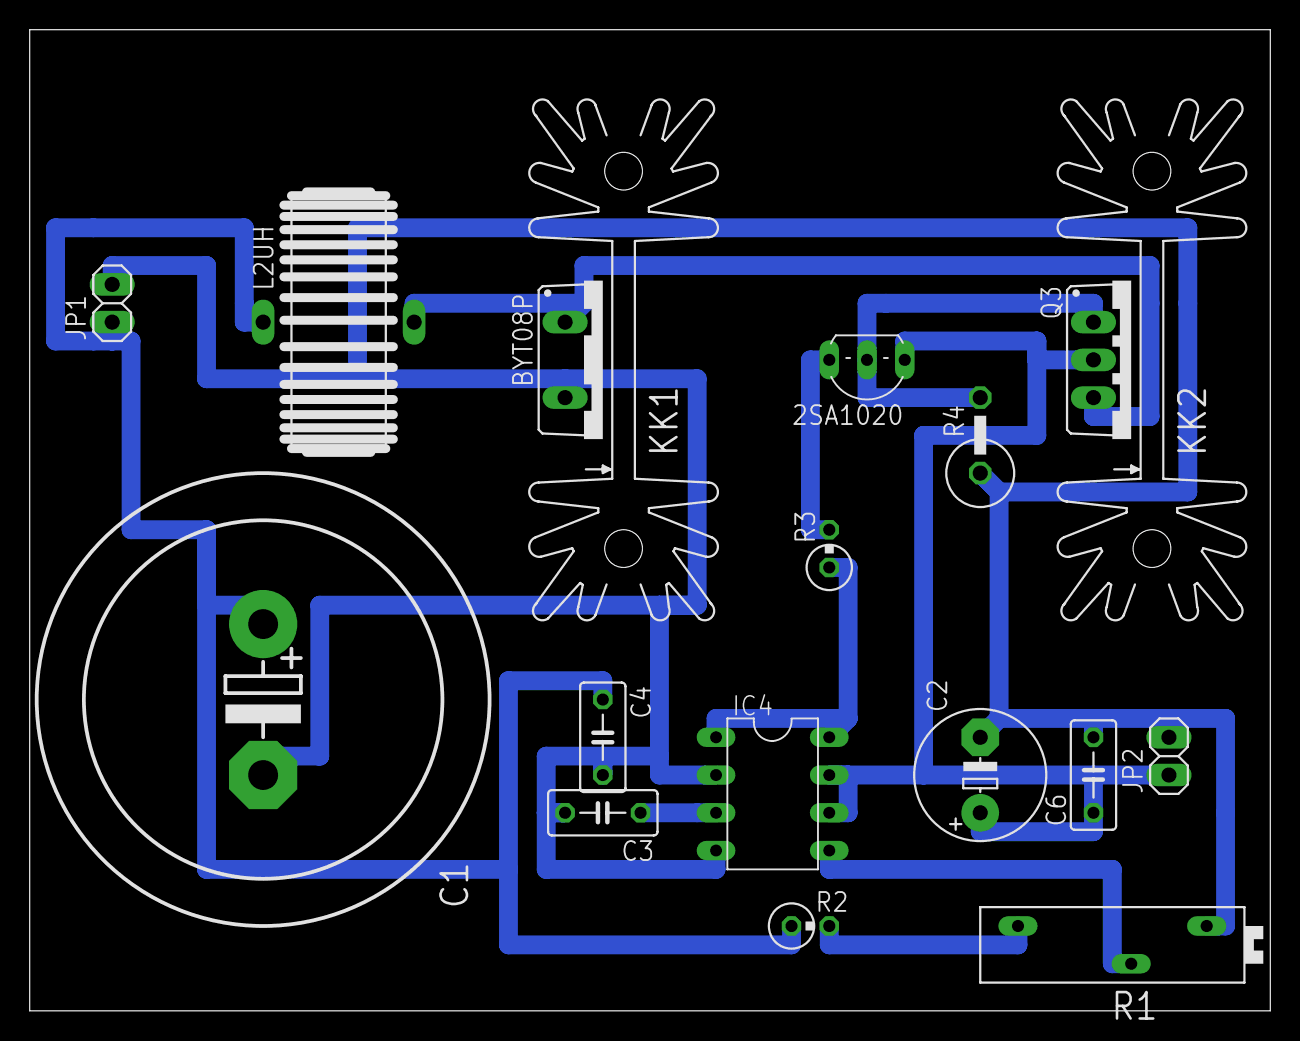
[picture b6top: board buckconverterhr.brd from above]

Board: 2 copper layers, 83.5 x 66.0 mm, 18 parts (0 on the bottom side), 10 nets.
